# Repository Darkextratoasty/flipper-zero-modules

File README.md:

# Flipper Zero hardware modules
This is a collection of PCBs for the various Flipper Zero GPIO expansion modules I've created.

# Modules

| Module                      | Design Completed | Board Tested | Case | Latest Version |
|-----------------------------|------------------|--------------|------|----------------|
| 20W IR Blaster (Simplified) | Yes              | No           | No   | v0.1           |
| 20W IR Blaster              | No               | No           | No   | N/A            |
| EDC-1                       | Yes              | No           | No   | v0.1           |
| ESP-01 Slim                 | Yes              | No           | No   | v0.1           |
| I2C & OneWire Probes        | Yes              | No           | No   | v0.1           |
| IR Blaster Mini             | Yes              | No           | No   | v0.2           |
| RS232 Serial                | Yes              | No           | No   | v0.1           |
| Slim CC1101 & NRF24L01      | Yes              | No           | No   | v0.1           |
## 20W IR Blaster (Simplified)
Highly experimental IR blaster that uses a supercapacitor to store and dump energy, allowing the board to push far more power through the IR LEDs than the Flipper Zero is capable of supplying on its own. By itself, the Flipper can supply up to 1.2A @ 5V and 1.2A @ 3.3V, however, due to battery limitations and SD card corruption risks, in practice it can supply about 5W max. By charging the supercapacitor at less than 5W, the Flipper's power rails never get stressed. The supercapacitor can then be disharged into the IR LEDs, allowing much more powerful bursts, in this case about 20W. The built in IR blaster is on the order of tens of milliwatts, or maybe 200x less powerful. As far as I'm aware, this is the most powerful IR blaster out there that's still powered by the Flipper Zero. 
This simplified version uses a resistor to limit the charge current of the supercapacitor and a comparator to limit the charge voltage to 3.3V. There is an indicator LED on board that shows when the cap is charged enough to fire. 
## 20W IR Blaster
This is the same idea as the simplified version above, but includes some nice features as well.
1. The supercapacitor is charged with a dedicated IC designed for exactly this purpose, meaning it doesn't waste power with resistors, so it burns less battery.
2. Includes temperature protection on the LEDs, meaning it will light up an error LED and refuse to fire if the LEDs are above a certain temperature.
3. Like the simplified version, it has an indicator LED to show when the supercapacitor is charged enough to fire, but it also will refuse to fire if there is not enough charge. 
4. Includes a boost-converter that allows the supercapacitor to charge up to about 7V, enabling two sets of LEDs to be placed in series, potentially doubling the IR output power.
Note: this board design has not yet been completed, so it is still theoretical. Also the name will probably have to change to reflect the actual power once designed.
## EDC-1
This is the first EDC or Every Day Carry board, designed to be small and pack as many useful features in as possible. There are four parts to this board:
1. A \~0.5W flashlight that runs off the 5V rail and uses pin C3 to turn on and off.
2. A Seeedstudio Xiao footprint that can accept several different ESP32 variant board for things like Marauder\*, Ghost ESP\*, WiFi Scanner, flipHTTP, and more. Pins connected are RX, TX, and two GPIO pins for other interactions, such as the module presence check that the WiFi Scanner app uses. The ESP is powered from the 5V rail using its own onboard regulator.
3. A DS18B20 temperature probe connected to pin 10 for quickly getting the ambient air temperature\*\*.
4. A QWIIC connector for attaching I2C peripherals such as environmental sensors or Wii Nunchucks to the flipper. These run on the 3.3V pin, so power hungry devices should be powered externally. 
\* there is no microSD card slot, so functionality may be limited.
\*\* since the sensor is mounted to the PCB, which is also used to dissipate heat from the LEDs and holds the Xiao ESP32, the reading may not be accurate for a while after using the flashlight or ESP. 
## ESP-01 Slim
Very simple module that allows an ESP8266 ESP-01 to be mounted nearly flush with the Flipper Zero for apps such as the WiFi Scanner. The ESP is powered from the 3.3V rail, but there are a few capacitors to help smooth out any current spikes that it might draw, so it should be safe with no risk of SD corruption.
## I2C & OneWire Probes
This board includes one QWIIC connector that can be used for I2C peripherals and three 3.5mm headphone-style jacks that can be used to attach either I2C or OneWire (eg. DS18B20 temperature sensor) devices. The folder shows a couple of example devices, including long waterproof DS18B20 temperature sensor probes, short direct connect SHT35 temperature and humidity sensor probes, and some others. 
## IR Blaster Mini
A much simpler IR blaster than the 20W ones, this uses the more traditional driving method of a simple resistor to set the current and draws power directly from the 5V pin. The output is somewhere around 4W, which is on par with most of the high powered IR blasters on the market currently.
## RS232 Serial
Uses an SP3232 to convert the Flipper Zero's 3.3V TTL UART into true ±10V RS232 signals, which are then presented on both male and female DP9 connectors. These connectors share the same signals, so they cannot be used independently or at the same time. 
## Slim CC1101 & NRF24L01
This is my version of the classic breakout boards that includes a 3.3V regulator, smoothing capacitors, and a footprint for the CC1101 and NRF24L01 radio modules. It actually has two footprints, one for the CC1101 and shorted NRF24L01 modules and one for the longer NRF24L01+PA+LNA modules so it doesn't end up sticking way out over the edge of the Flipper. With some patience, good quality solder, and the plated-hole breakaway board, the modules can be soldered in place without using pins, such that the board sits completely flat against the Flipper, making it very low profile.

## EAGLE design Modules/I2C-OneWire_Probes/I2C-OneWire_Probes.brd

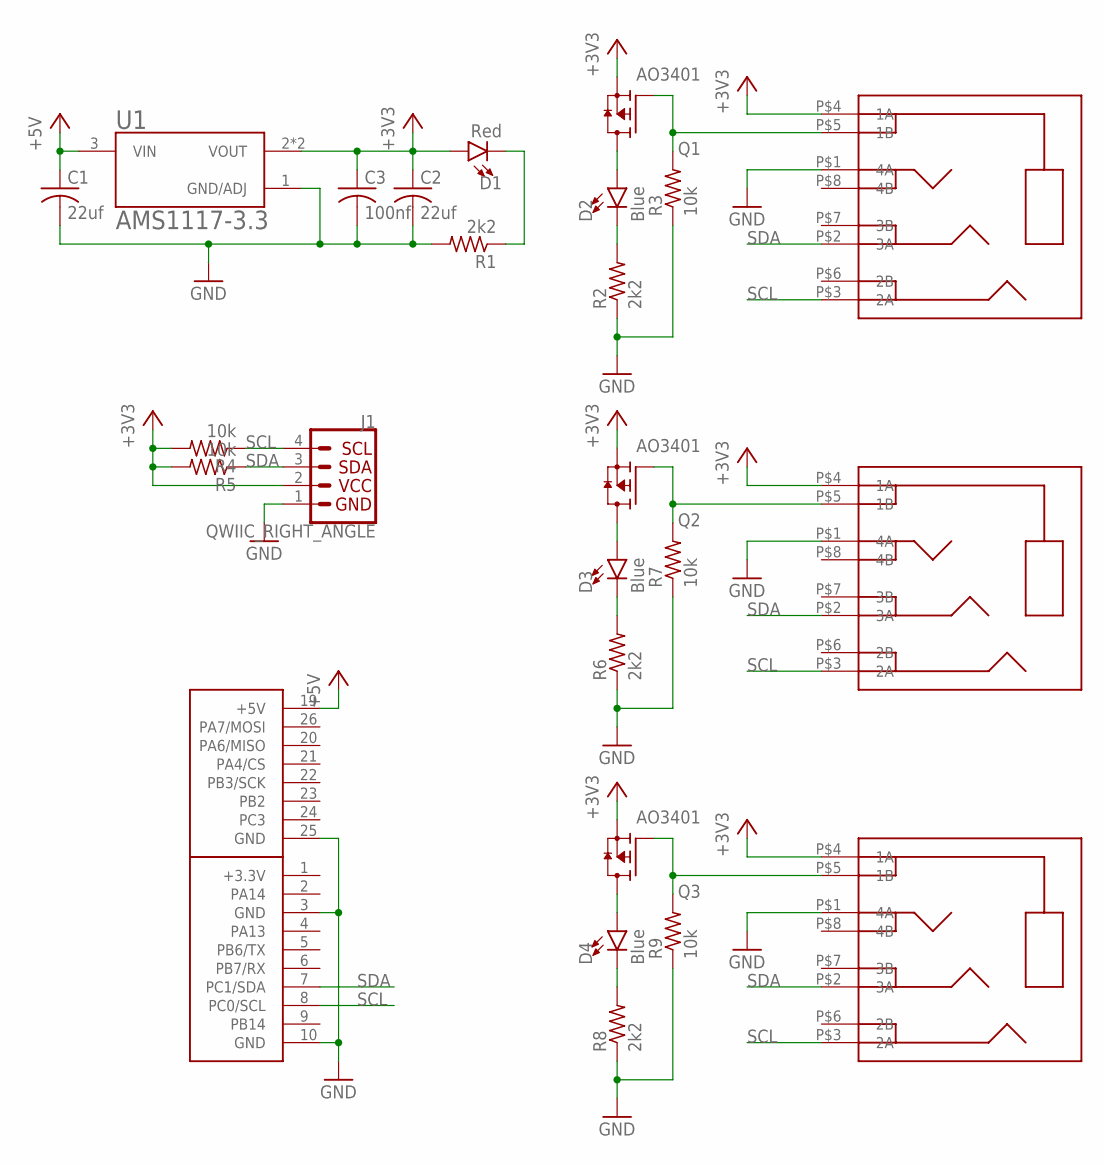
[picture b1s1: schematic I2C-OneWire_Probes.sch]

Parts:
C1, C2: 22uf; C3216
C3: 100nf; C0805
D1: Red; LED-1206
D2, D3, D4: Blue; LED-1206
J1: QWIIC_RIGHT_ANGLE; JST04_1MM_RA
Q1, Q2, Q3: AO3401
R1, R2, R6, R8: 2k2; R0805
R3, R4, R5, R7, R9: 10k; R0805
U1: AMS1117-3.3; SOT229P700X180-4N
U$1: BOTH-SMD
U$2, U$3, U$4: PJ-3938PJ

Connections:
+3V3: C2.1, C3.1, D1.A, J1.2, Q1.2 (S), Q2.2 (S), Q3.2 (S), R4.2, R5.2, U1.2 (VOUT), U1.4 (VOUT), U$2.P$4 (1A), U$3.P$4 (1A), U$4.P$4 (1A)
+5V: C1.1, U1.3 (VIN), U$1.19 (+5V)
GND: C1.2, C2.2, C3.2, J1.1, R1.2, R2.1, R3.1, R6.1, R7.1, R8.1, R9.1, U1.1 (GND/ADJ), U$1.3 (GND), U$1.10 (GND), U$1.25 (GND), U$2.P$1 (4A), U$3.P$1 (4A), U$4.P$1 (4A)
unnamed: D2.A, Q1.3 (D)
unnamed: D2.C, R2.2
unnamed: Q1.1 (G), R3.2, U$2.P$5 (1B)
unnamed: D3.C, R6.2
unnamed: Q2.1 (G), R7.2, U$3.P$5 (1B)
unnamed: D4.C, R8.2
unnamed: Q3.1 (G), R9.2, U$4.P$5 (1B)
unnamed: D1.C, R1.1
unnamed: D3.A, Q2.3 (D)
unnamed: D4.A, Q3.3 (D)
SCL: J1.4, R4.1, U$1.8 (PC0/SCL), U$2.P$3 (2A), U$3.P$3 (2A), U$4.P$3 (2A)
SDA: J1.3, R5.1, U$1.7 (PC1/SDA), U$2.P$2 (3A), U$3.P$2 (3A), U$4.P$2 (3A)

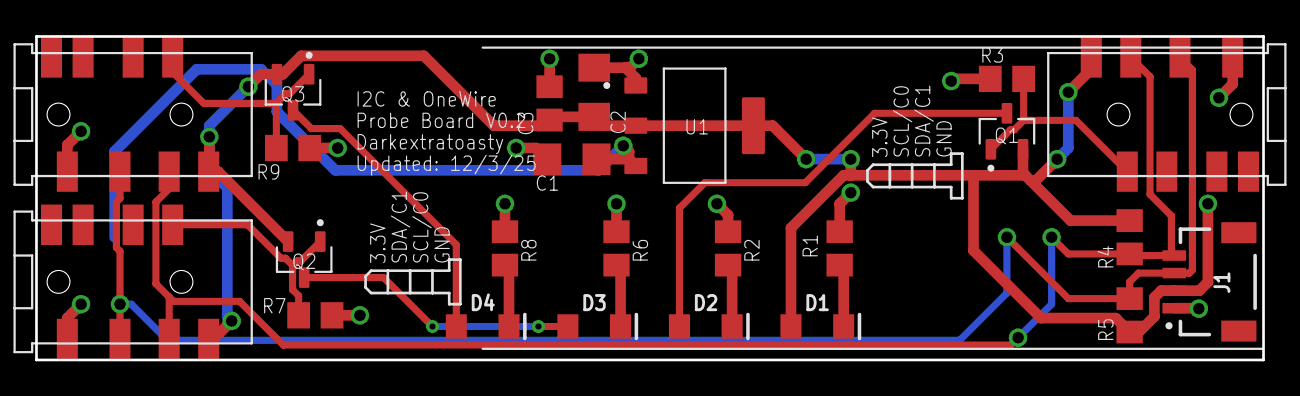
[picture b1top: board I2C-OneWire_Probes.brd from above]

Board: 2 copper layers, 69.8 x 18.4 mm, 25 parts (0 on the bottom side), 15 nets.

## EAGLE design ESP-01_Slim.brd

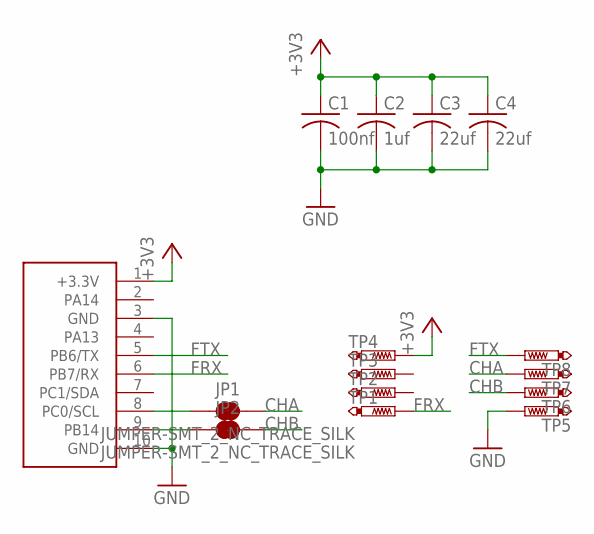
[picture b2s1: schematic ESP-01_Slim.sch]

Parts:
C1: 100nf; C0805
C2: 1uf; C0805
C3, C4: 22uf; C3216
JP1, JP2: JUMPER-SMT_2_NC_TRACE_SILK; SMT-JUMPER_2_NC_TRACE_SILK
TP1, TP2, TP3, TP4, TP5, TP6, TP7, TP8: PTR1B1,27; B1,27
U$2: RIGHT-H2-SMD

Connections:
+3V3: C1.1, C2.1, C3.1, C4.1, TP4.TP, U$2.1 (+3.3V)
CHA: JP1.2, TP7.TP
CHB: JP2.2, TP6.TP
FRX: TP1.TP, U$2.6 (PB7/RX)
FTX: TP8.TP, U$2.5 (PB6/TX)
GND: C1.2, C2.2, C3.2, C4.2, TP5.TP, U$2.3 (GND), U$2.10 (GND)
unnamed: JP1.1, U$2.8 (PC0/SCL)
unnamed: JP2.1, U$2.9 (PB14)

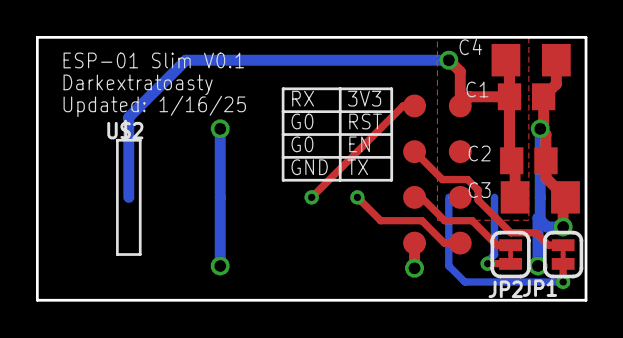
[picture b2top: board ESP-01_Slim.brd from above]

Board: 2 copper layers, 30.5 x 14.6 mm, 15 parts (0 on the bottom side), 8 nets.

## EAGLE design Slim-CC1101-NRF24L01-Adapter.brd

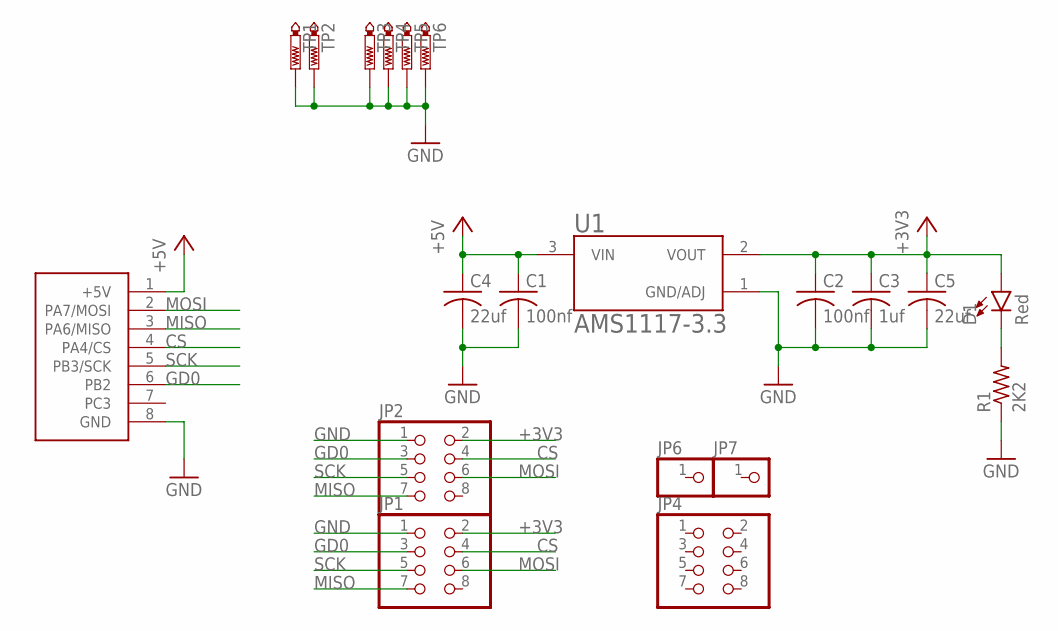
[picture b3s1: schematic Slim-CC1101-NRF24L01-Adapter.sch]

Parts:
C1, C2: 100nf; C0805
C3: 1uf; C0805
C4, C5: 22uf; C3216
D1: Red; LED-1206
JP1, JP2, JP4: PINHD-2X4; 2X04
JP6, JP7: PINHD-1X1; 1X01
R1: 2K2; R0805
TP1, TP2: PTR1B1,27; B1,27
TP3, TP4, TP5, TP6: PTR1B2,54; B2,54
U1: AMS1117-3.3; SOT229P700X180-4N
U$1: LEFT-H1-SMD

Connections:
+3V3: C2.1, C3.1, C5.1, D1.A, JP1.2, JP2.2, U1.2 (VOUT)
+5V: C1.1, C4.1, U1.3 (VIN), U$1.1 (+5V)
CS: JP1.4, JP2.4, U$1.4 (PA4/CS)
GD0: JP1.3, JP2.3, U$1.6 (PB2)
GND: C1.2, C2.2, C3.2, C4.2, C5.2, JP1.1, JP2.1, R1.1, TP1.TP, TP2.TP, TP3.TP, TP4.TP, TP5.TP, TP6.TP, U1.1 (GND/ADJ), U$1.8 (GND)
MISO: JP1.7, JP2.7, U$1.3 (PA6/MISO)
MOSI: JP1.6, JP2.6, U$1.2 (PA7/MOSI)
unnamed: D1.C, R1.2
SCK: JP1.5, JP2.5, U$1.5 (PB3/SCK)

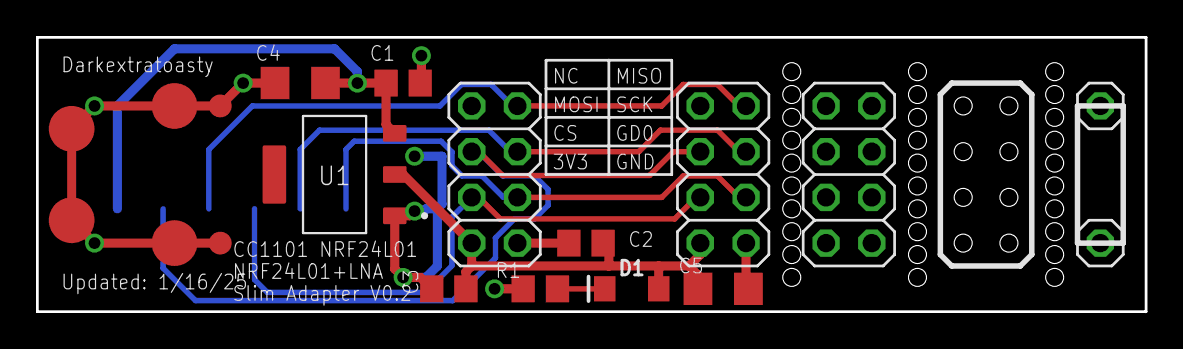
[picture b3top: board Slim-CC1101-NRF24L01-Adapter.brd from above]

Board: 2 copper layers, 61.6 x 15.2 mm, 20 parts (0 on the bottom side), 9 nets.

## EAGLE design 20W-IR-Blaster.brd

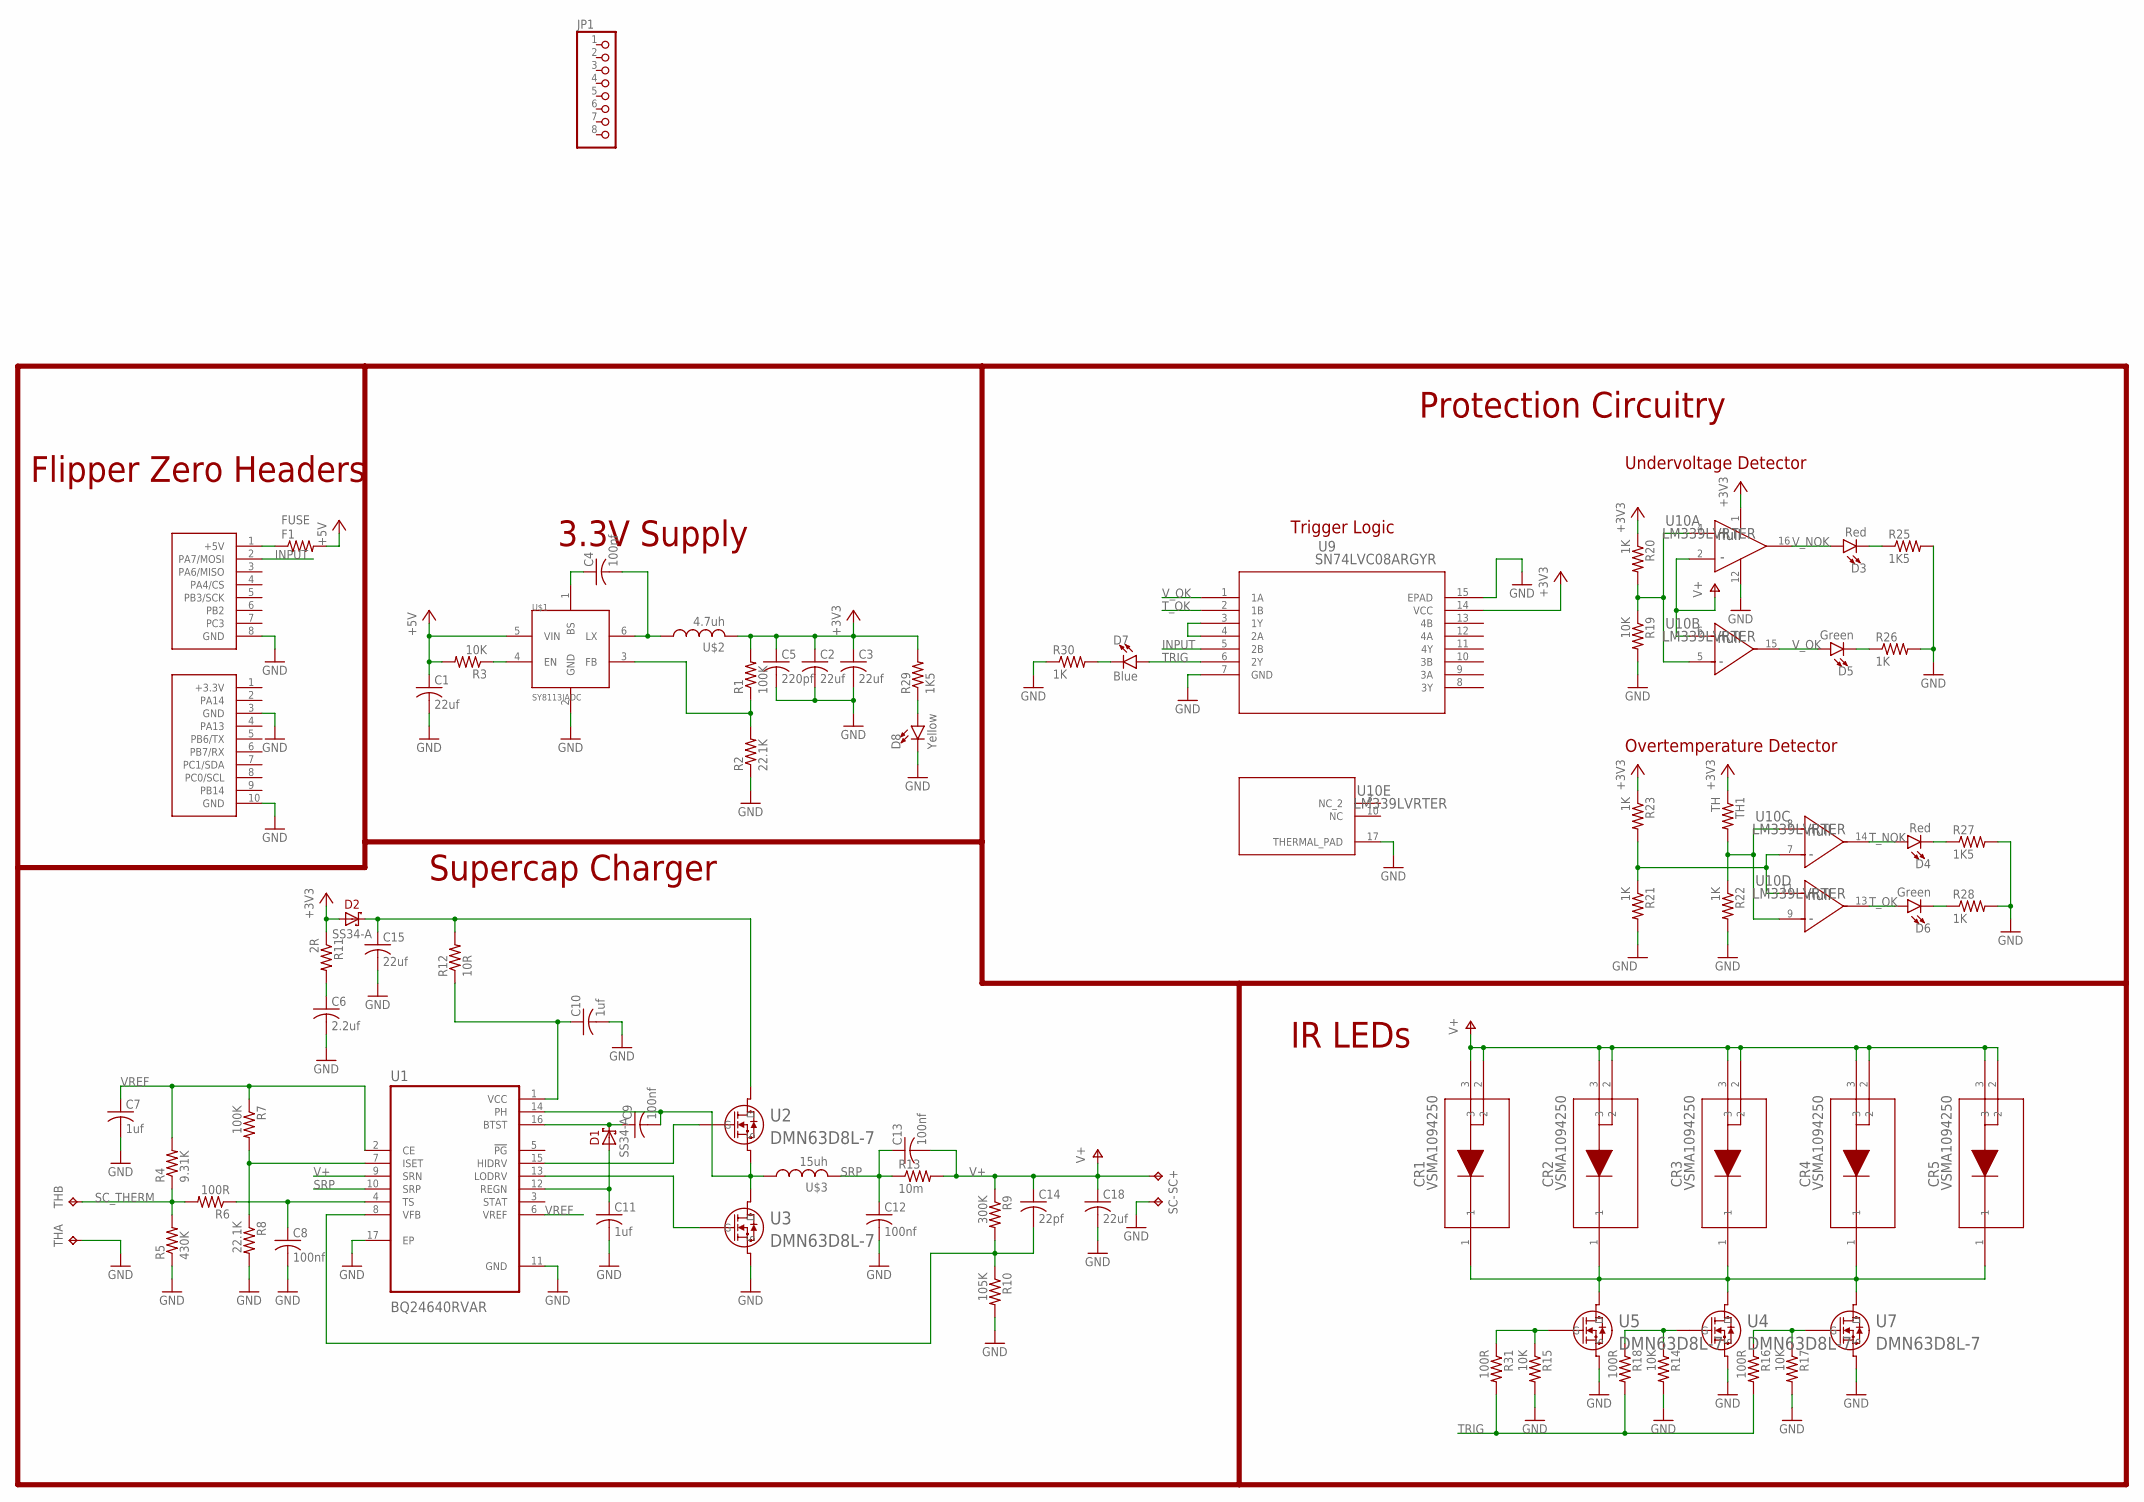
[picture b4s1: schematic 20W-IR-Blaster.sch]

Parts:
C1, C2, C3, C15, C18: 22uf; C3216
C4, C8, C9, C12, C13: 100nf; C0603
C5: 220pf; C0603
C6: 2.2uf; C0603
C7, C10, C11: 1uf; C0603
C14: 22pf; C0603
CR1, CR2, CR3, CR4, CR5: VSMA1094250; DIODE_VSMA1094250_VIS
D1, D2: SS34-A; DO-214AC
D3, D4: Red; LED-0603
D5, D6: Green; LED-0603
D7: Blue; LED-0603
D8: Yellow; LED-0603
F1: FUSE; R1206
JP1: PINHD-1X8; 1X08
R1, R7: 100K; R0603
R2, R8: 22.1K; R0603
R3, R14, R15, R17, R19: 10K; R0603
R4: 9.31K; R0603
R5: 430K; R0603
R6, R16, R18, R31: 100R; R0603
R9: 300K; R0603
R10: 105K; R0603
R11: 2R; R2512
R12: 10R; R2512
R13: 10m; R0805
R20, R21, R22, R23, R26, R28, R30: 1K; R0603
R25, R27, R29: 1K5; R0603
SC+: TPPAD1-20Y; P1-20Y
SC-: TPPAD1-20Y; P1-20Y
TH: TP2P2-38-17; P2-38-17
TH1: TH; R0603
U1: BQ24640RVAR; QFN50P350X350X100-17N
U2, U3, U4, U5, U7: DMN63D8L-7; SOIC_63D8L-7_DIO
U9: SN74LVC08ARGYR; RGY14_2P05X2P05
U10: LM339LVRTER; RTE0016C-IPC_A
U$1: SY8113IADC; TSOT6
U$2: 4.7uh; CYH127-4.7UH
U$3: 15uh; CYH127-4.7UH
U$4: LEFT-H1-SMD
U$5: RIGHT-H2-SMD

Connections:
+3V3: C2.1, C3.1, C5.1, D2.A, R1.2, R11.1, R20.1, R23.1, R29.2, TH1.1, U9.14 (VCC), U10.1 (V+), U$2.P$2 (2)
+5V: C1.1, F1.2, R3.2, U$1.5 (VIN)
GND: C1.2, C2.2, C3.2, C5.2, C6.2, C7.2, C8.2, C10.2, C11.2, C12.2, C15.2, C18.2, D8.C, R2.1, R5.1, R8.2, R10.2, R14.2, R15.2, R17.2, R19.2, R21.2, R22.2, R25.2, R26.2, R27.2, R28.2, R30.1, SC-.TP, TH.TP-1, U1.11 (GND), U1.17 (EP), U3.3 (S), U4.3 (S), U5.3 (S), U7.3 (S), U9.7 (GND), U9.15 (EPAD), U10.12 (GND), U10.17 (THERMAL_PAD), U$1.2 (GND), U$4.8 (GND), U$5.3 (GND), U$5.10 (GND)
INPUT: U9.5 (2B), U$4.2 (PA7/MOSI)
unnamed: R3.1, U$1.4 (EN)
unnamed: C4.1, U$1.1 (BS)
unnamed: C4.2, U$1.6 (LX), U$2.P$1 (1)
unnamed: C9.2, U1.14 (PH), U2.3 (S), U3.2 (D), U$3.P$1 (1)
unnamed: R1.1, R2.2, U$1.3 (FB)
unnamed: C6.1, R11.2
unnamed: C15.1, D2.C, R12.2, U2.2 (D)
unnamed: C10.1, R12.1, U1.1 (VCC)
unnamed: U1.15 (HIDRV), U2.1 (G)
unnamed: U1.13 (LODRV), U3.1 (G)
unnamed: C9.1, D1.C, U1.16 (BTST)
unnamed: C11.1, D1.A, U1.12 (REGN)
unnamed: CR1.1, CR2.1, CR3.1, CR4.1, CR5.1, U4.2 (D), U5.2 (D), U7.2 (D)
unnamed: R19.1, R20.2, U10.4 (IN1+), U10.5 (IN2-)
unnamed: R15.1, R31.1, U5.1 (G)
unnamed: C14.2, R9.2, R10.1, U1.8 (VFB)
unnamed: C8.1, R6.1, U1.4 (TS)
unnamed: F1.1, U$4.1 (+5V)
unnamed: R14.1, R18.1, U4.1 (G)
unnamed: R21.1, R23.2, U10.7 (IN3-), U10.11 (IN4+)
unnamed: R16.1, R17.1, U7.1 (G)
unnamed: U9.3 (1Y), U9.4 (2A)
unnamed: R7.2, R8.1, U1.7 (ISET)
unnamed: R22.1, TH1.2, U10.8 (IN3+), U10.9 (IN4-)
unnamed: D3.C, R25.1
unnamed: D5.C, R26.1
unnamed: D4.C, R27.1
unnamed: D6.C, R28.1
unnamed: D8.A, R29.1
unnamed: D7.C, R30.2
SC_THERM: R4.1, R5.2, R6.2, TH.TP-2
SRP: C12.1, C13.1, R13.1, U1.10 (SRP), U$3.P$2 (2)
TRIG: D7.A, R16.2, R18.2, R31.2, U9.6 (2Y)
T_NOK: D4.A, U10.14 (OUT3)
T_OK: D6.A, U9.2 (1B), U10.13 (OUT4)
V+: C13.2, C14.1, C18.1, CR1.2, CR1.3, CR2.2, CR2.3, CR3.2, CR3.3, CR4.2, CR4.3, CR5.2, CR5.3, R9.1, R13.2, SC+.TP, U1.9 (SRN), U10.2 (IN1-), U10.6 (IN2+)
VREF: C7.1, R4.2, R7.1, U1.2 (CE), U1.6 (VREF)
V_NOK: D3.A, U10.16 (OUT1)
V_OK: D5.A, U9.1 (1A), U10.15 (OUT2)

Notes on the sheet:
3.3V Supply
Supercap Charger
Flipper Zero Headers
Trigger Logic
Undervoltage Detector
Overtemperature Detector
Protection Circuitry
IR LEDs

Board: 2 copper layers, 78 parts (7 on the bottom side), 43 nets, no tracks yet.

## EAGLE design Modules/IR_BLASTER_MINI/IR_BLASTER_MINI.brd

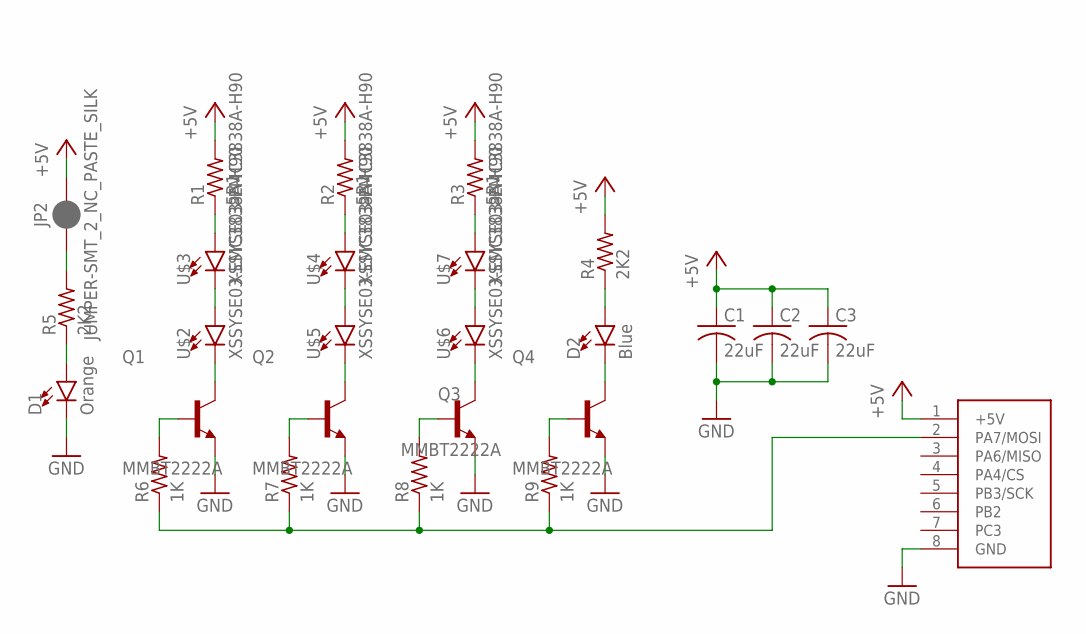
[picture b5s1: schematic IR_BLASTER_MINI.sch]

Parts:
C1, C2, C3: 22uF; C3216
D1: Orange; LED-0603
D2: Blue; LED-0603
JP2: JUMPER-SMT_2_NC_PASTE_SILK; SMT-JUMPER_2_NC_PASTE_SILK
Q1, Q2, Q3, Q4: MMBT2222A; SOT95P240X120-3N
R1, R2, R3: 5R1; R2512
R4, R5: 2K2; R0603
R6, R7, R8, R9: 1K; R0603
U$1: LEFT-H1-SMD
U$2, U$3, U$4, U$5, U$6, U$7: XSSYSE03-EMC3838A-H90

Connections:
+5V: C1.1, C2.1, C3.1, JP2.2, R1.2, R2.2, R3.2, R4.2, U$1.1 (+5V)
GND: C1.2, C2.2, C3.2, D1.C, Q1.2 (E), Q2.2 (E), Q3.2 (E), Q4.2 (E), U$1.8 (GND)
unnamed: D1.A, R5.1
unnamed: Q1.1 (B), R6.2
unnamed: Q1.3 (C), U$2.P$2 (C)
unnamed: U$2.P$1 (A), U$3.P$2 (C)
unnamed: R1.1, U$3.P$1 (A)
unnamed: R2.1, U$4.P$1 (A)
unnamed: U$4.P$2 (C), U$5.P$1 (A)
unnamed: Q2.3 (C), U$5.P$2 (C)
unnamed: Q2.1 (B), R7.2
unnamed: Q3.1 (B), R8.2
unnamed: Q3.3 (C), U$6.P$2 (C)
unnamed: U$6.P$1 (A), U$7.P$2 (C)
unnamed: R3.1, U$7.P$1 (A)
unnamed: D2.A, R4.1
unnamed: D2.C, Q4.3 (C)
unnamed: Q4.1 (B), R9.2
unnamed: JP2.1, R5.2
unnamed: R6.1, R7.1, R8.1, R9.1, U$1.2 (PA7/MOSI)

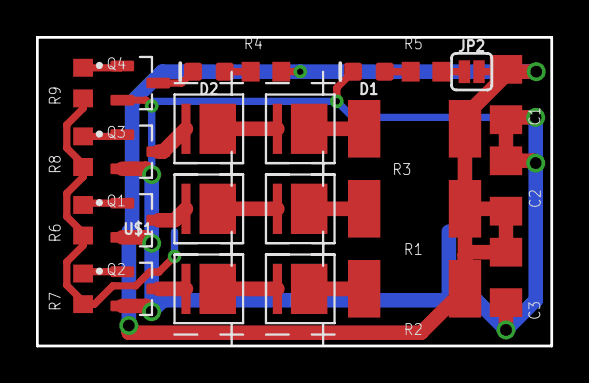
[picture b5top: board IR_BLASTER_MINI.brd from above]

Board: 2 copper layers, 28.6 x 17.1 mm, 26 parts (0 on the bottom side), 20 nets.

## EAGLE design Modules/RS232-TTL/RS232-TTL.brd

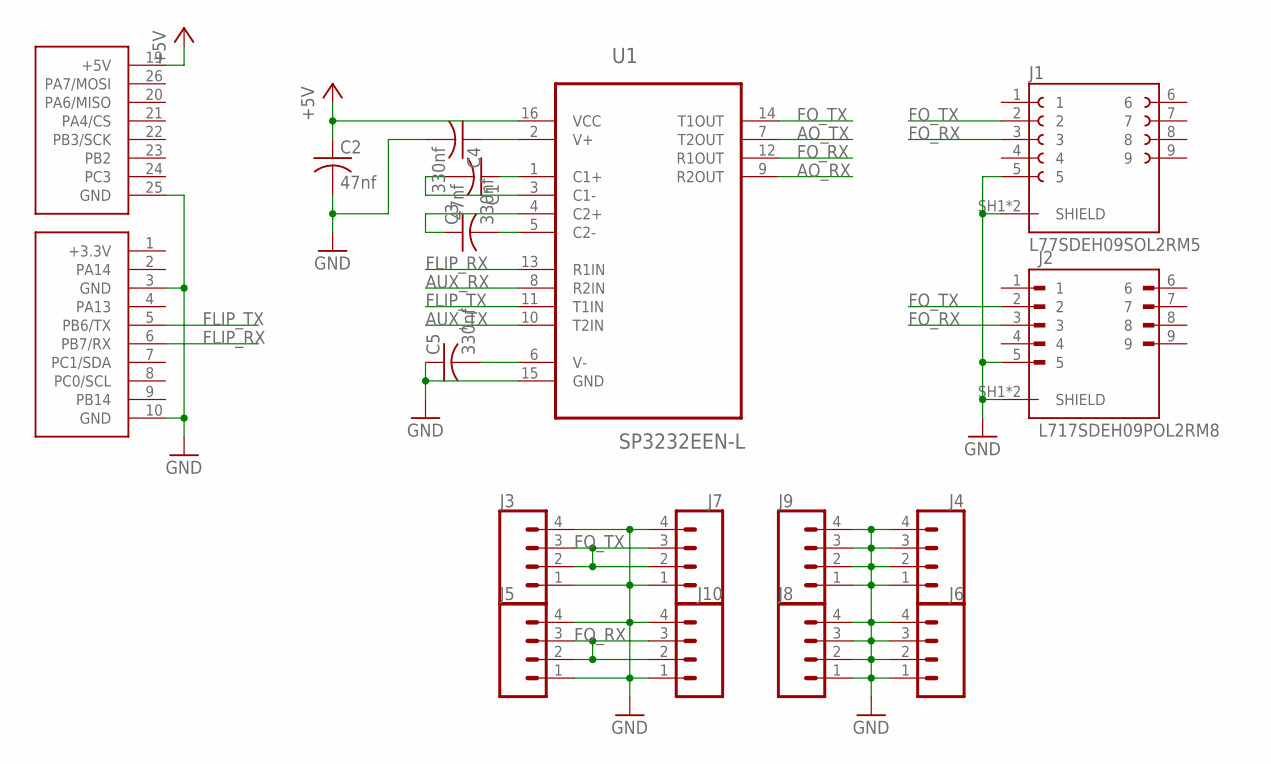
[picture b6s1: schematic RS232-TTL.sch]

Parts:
C1, C2: 47nf; C0805
C3, C4, C5: 330nf; C0805
J1: L77SDEH09SOL2RM5; AMPHENOL_L77SDEH09SOL2RM5
J2: L717SDEH09POL2RM8; AMPHENOL_L717SDEH09POL2RM8
J3, J4, J5, J6: CONN_04SMD_VERTICAL_MALE; 1X04_SMD_VERTICAL_COMBO_CENTERED
J7, J8, J9, J10: CONN_04PTH; 1X04
U1: SP3232EEN-L; SOIC127P600X175-16N
U$1: BOTH-SMD

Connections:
+5V: C2.1, U1.16 (VCC), U$1.19 (+5V)
AO_RX: U1.9 (R2OUT)
AO_TX: U1.7 (T2OUT)
AUX_RX: U1.8 (R2IN)
AUX_TX: U1.10 (T2IN)
FLIP_RX: U1.13 (R1IN), U$1.6 (PB7/RX)
FLIP_TX: U1.11 (T1IN), U$1.5 (PB6/TX)
FO_RX: J1.3, J2.3, J5.2, J5.3, J10.2, J10.3, U1.12 (R1OUT)
FO_TX: J1.2, J2.2, J3.2, J3.3, J7.2, J7.3, U1.14 (T1OUT)
GND: C2.2, C4.2, C5.1, J1.5, J1.SH1 (SHIELD), J1.SH2 (SHIELD), J2.5, J2.SH1 (SHIELD), J2.SH2 (SHIELD), J3.1, J3.4, J4.1, J4.2, J4.3, J4.4, J5.1, J5.4, J6.1, J6.2, J6.3, J6.4, J7.1, J7.4, J8.1, J8.2, J8.3, J8.4, J9.1, J9.2, J9.3, J9.4, J10.1, J10.4, U1.15 (GND), U$1.3 (GND), U$1.10 (GND), U$1.25 (GND)
unnamed: C4.1, U1.2 (V+)
unnamed: C1.1, U1.1 (C1+)
unnamed: C3.2, U1.5 (C2-)
unnamed: C3.1, U1.4 (C2+)
unnamed: C1.2, U1.3 (C1-)
unnamed: C5.2, U1.6 (V-)

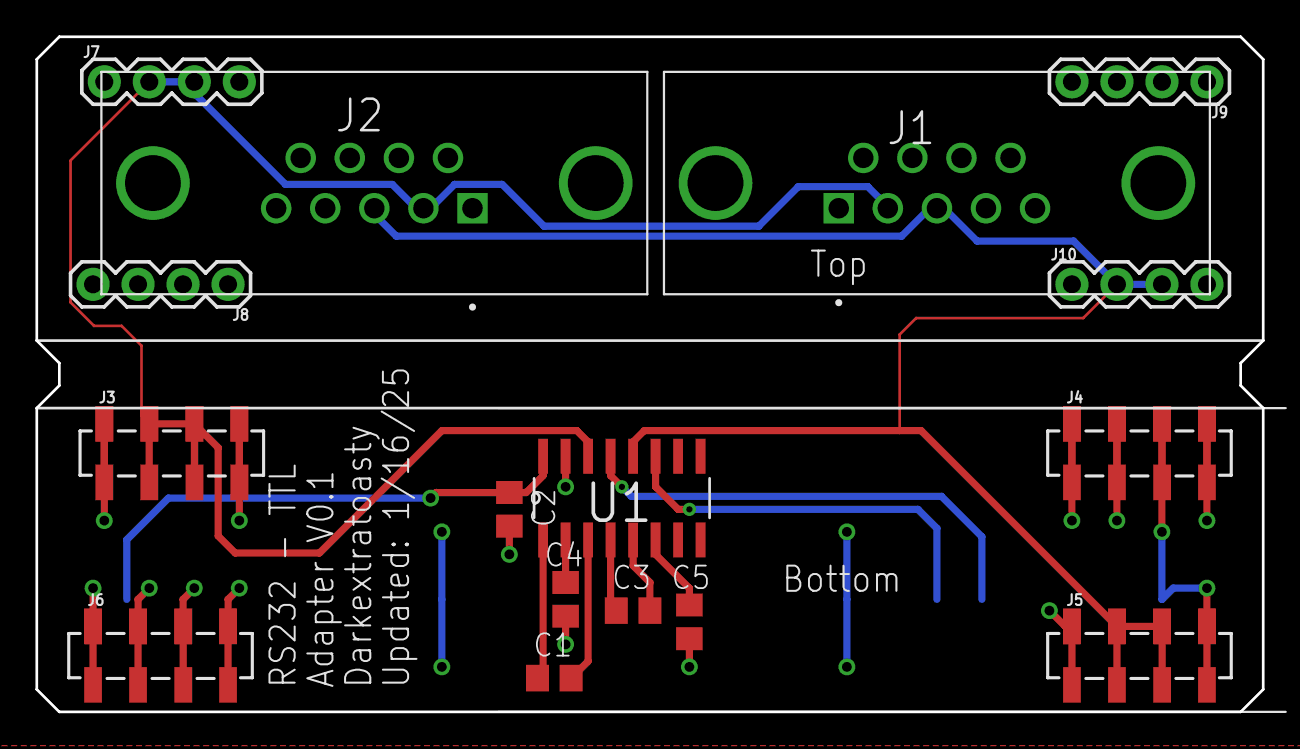
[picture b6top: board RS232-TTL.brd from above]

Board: 2 copper layers, 69.2 x 38.1 mm, 17 parts (0 on the bottom side), 12 nets.

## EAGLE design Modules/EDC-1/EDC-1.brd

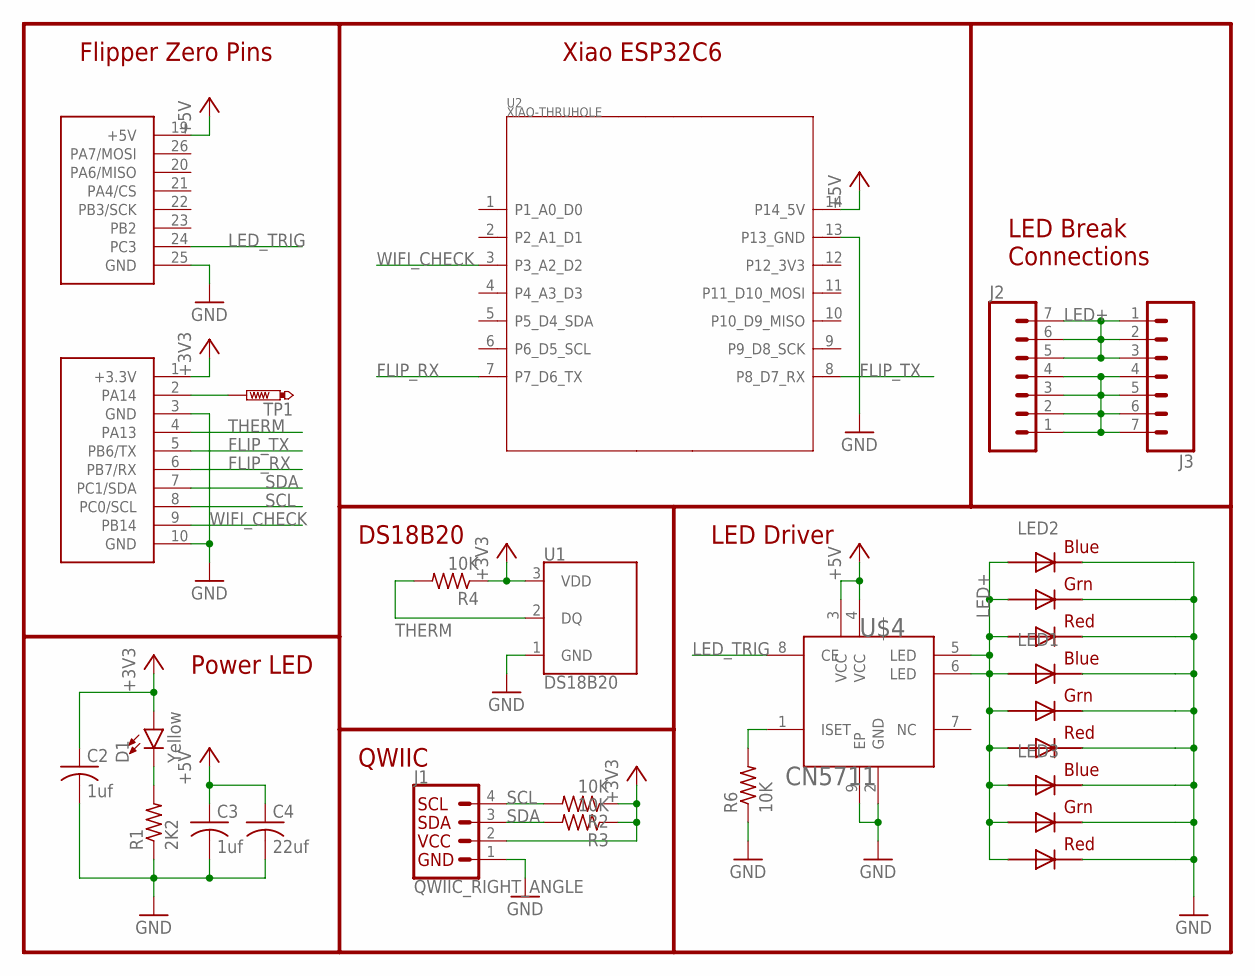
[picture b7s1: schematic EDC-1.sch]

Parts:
C2, C3: 1uf; C0805
C4: 22uf; C3216
D1: Yellow; LED-1206
J1: QWIIC_RIGHT_ANGLE; JST04_1MM_RA
J2, J3: CONN_07LONGPADS; 1X07_LONGPADS
LED1, LED2, LED3: RGBLED5050
R1: 2K2; R0805
R2, R3, R4, R6: 10K; R0805
TP1: PTR1PAD1-13; P1-13
U1: DS18B20; TO-92-AMMO
U2: XIAO-THRUHOLE; XIAO-GENERIC-THRUHOLE-MODULE14P-2.54-21X17.8MM
U$1: BOTH-SMD
U$4: CN5711; SOIC127P600X175-9N

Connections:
+3V3: C2.1, D1.A, J1.2, R2.1, R3.1, R4.1, U1.3 (VDD), U$1.1 (+3.3V)
+5V: C3.1, C4.1, U2.14 (P14_5V), U$1.19 (+5V), U$4.3 (VCC), U$4.4 (VCC)
FLIP_RX: U2.7 (P7_D6_TX), U$1.6 (PB7/RX)
FLIP_TX: U2.8 (P8_D7_RX), U$1.5 (PB6/TX)
GND: C2.2, C3.2, C4.2, J1.1, J2.1, J2.2, J2.3, J2.4, J3.4, J3.5, J3.6, J3.7, LED1.4 (BLUE_C), LED1.5 (RED_C), LED1.6 (GREEN_C), LED2.4 (BLUE_C), LED2.5 (RED_C), LED2.6 (GREEN_C), LED3.4 (BLUE_C), LED3.5 (RED_C), LED3.6 (GREEN_C), R1.1, R6.1, U1.1 (GND), U2.13 (P13_GND), U$1.3 (GND), U$1.10 (GND), U$1.25 (GND), U$4.2 (GND), U$4.9 (EP)
LED+: J2.5, J2.6, J2.7, J3.1, J3.2, J3.3, LED1.1 (GREEN_A), LED1.2 (RED_A), LED1.3 (BLUE_A), LED2.1 (GREEN_A), LED2.2 (RED_A), LED2.3 (BLUE_A), LED3.1 (GREEN_A), LED3.2 (RED_A), LED3.3 (BLUE_A), U$4.5 (LED), U$4.6 (LED)
LED_TRIG: U$1.24 (PC3), U$4.8 (CE)
unnamed: TP1.TP, U$1.2 (PA14)
unnamed: R6.2, U$4.1 (ISET)
unnamed: D1.C, R1.2
SCL: J1.4, R2.2, U$1.8 (PC0/SCL)
SDA: J1.3, R3.2, U$1.7 (PC1/SDA)
THERM: R4.2, U1.2 (DQ), U$1.4 (PA13)
WIFI_CHECK: U2.3 (P3_A2_D2), U$1.9 (PB14)

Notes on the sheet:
Flipper Zero Pins
Xiao ESP32C6
LED Break Connections
LED Driver
DS18B20
QWIIC
Power LED

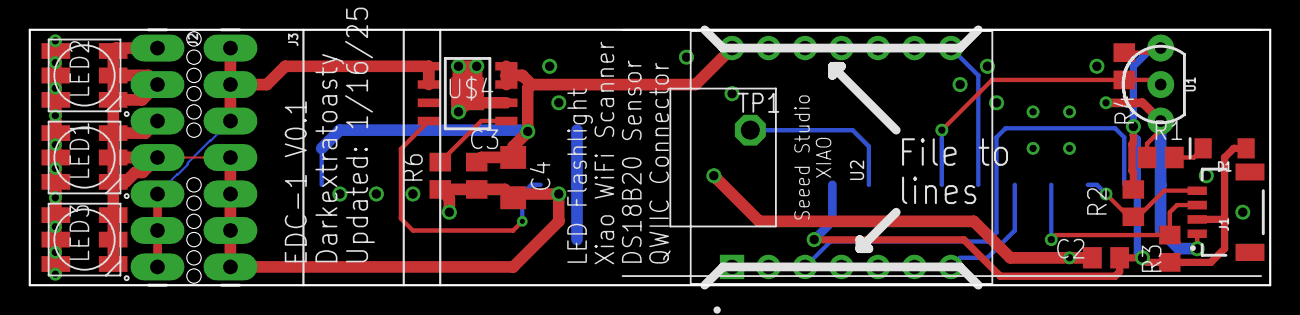
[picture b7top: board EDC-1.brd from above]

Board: 2 copper layers, 86.4 x 17.8 mm, 20 parts (0 on the bottom side), 14 nets.

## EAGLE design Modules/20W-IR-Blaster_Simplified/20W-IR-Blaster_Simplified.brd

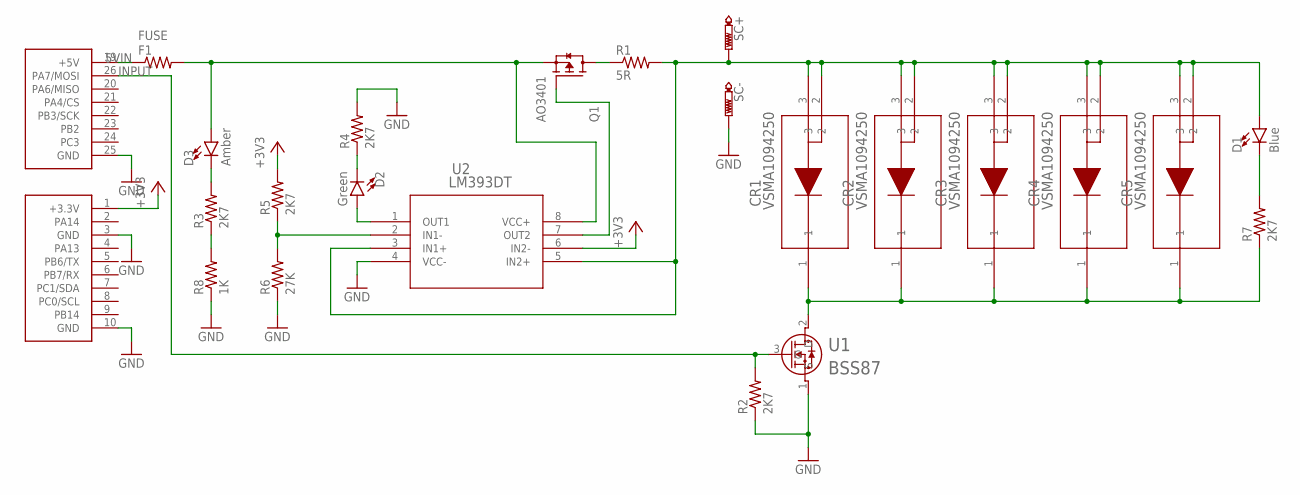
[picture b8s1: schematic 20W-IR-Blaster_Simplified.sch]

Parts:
CR1, CR2, CR3, CR4, CR5: VSMA1094250; DIODE_VSMA1094250_VIS
D1: Blue; LED-1206
D2: Green; LED-1206
D3: Amber; LED-1206
F1: FUSE; R1206
Q1: AO3401
R1: 5R; R2512
R2, R3, R4, R5, R7: 2K7; R0805
R6: 27K; R0805
R8: 1K; R0805
SC+: PTR1PAD1-20Y; P1-20Y
SC-: PTR1PAD1-20Y; P1-20Y
U1: BSS87; SOT89_NXP
U2: LM393DT; SO8_STM
U$1: BOTH-SMD

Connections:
5VIN: F1.1, U$1.19 (+5V)
+3V3: R5.2, U2.6 (IN2-), U$1.1 (+3.3V)
GND: R2.1, R4.2, R6.1, R8.1, SC-.TP, U1.1 (S), U2.4 (VCC-), U$1.3 (GND), U$1.10 (GND), U$1.25 (GND)
INPUT: R2.2, U1.3 (G), U$1.26 (PA7/MOSI)
unnamed: Q1.3 (D), R1.1
unnamed: CR1.2, CR1.3, CR2.2, CR2.3, CR3.2, CR3.3, CR4.2, CR4.3, CR5.2, CR5.3, D1.A, R1.2, SC+.TP, U2.3 (IN1+), U2.5 (IN2+)
unnamed: D2.A, U2.1 (OUT1)
unnamed: R5.1, R6.2, U2.2 (IN1-)
unnamed: Q1.1 (G), U2.7 (OUT2)
unnamed: D2.C, R4.1
unnamed: D1.C, R7.2
unnamed: D3.C, R3.2
unnamed: R3.1, R8.2
unnamed: D3.A, F1.2, Q1.2 (S), U2.8 (VCC+)
unnamed: CR1.1, CR2.1, CR3.1, CR4.1, CR5.1, R7.1, U1.2 (D)

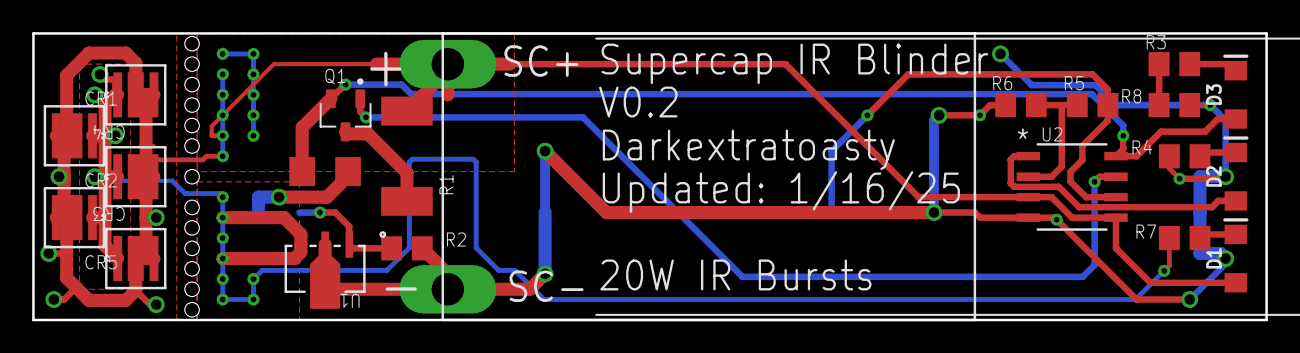
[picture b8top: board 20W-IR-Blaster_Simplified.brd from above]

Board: 2 copper layers, 76.5 x 17.8 mm, 23 parts (0 on the bottom side), 15 nets.

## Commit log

2025-01-21 cleaned up structure a bit
2025-01-21 more restructuring and updated readme
2025-01-21 in the process of creating BOMs
2025-01-22 pushed boards to fusion360
2025-12-03 fixed pinout for 3.5mm jacks on I2C-OneWire-Probes
2025-12-03 fixed silkscreen on I2C-OneWire-Probes

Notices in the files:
parts and their libraries:
SparkFun-LED: Licensing: Creative Commons ShareAlike 4.0 International - https://creativecommons.org/licenses/by-sa/4.0
COPYRIGHT: Copyright (C) 2025 Ultra Librarian. All rights reserved.
